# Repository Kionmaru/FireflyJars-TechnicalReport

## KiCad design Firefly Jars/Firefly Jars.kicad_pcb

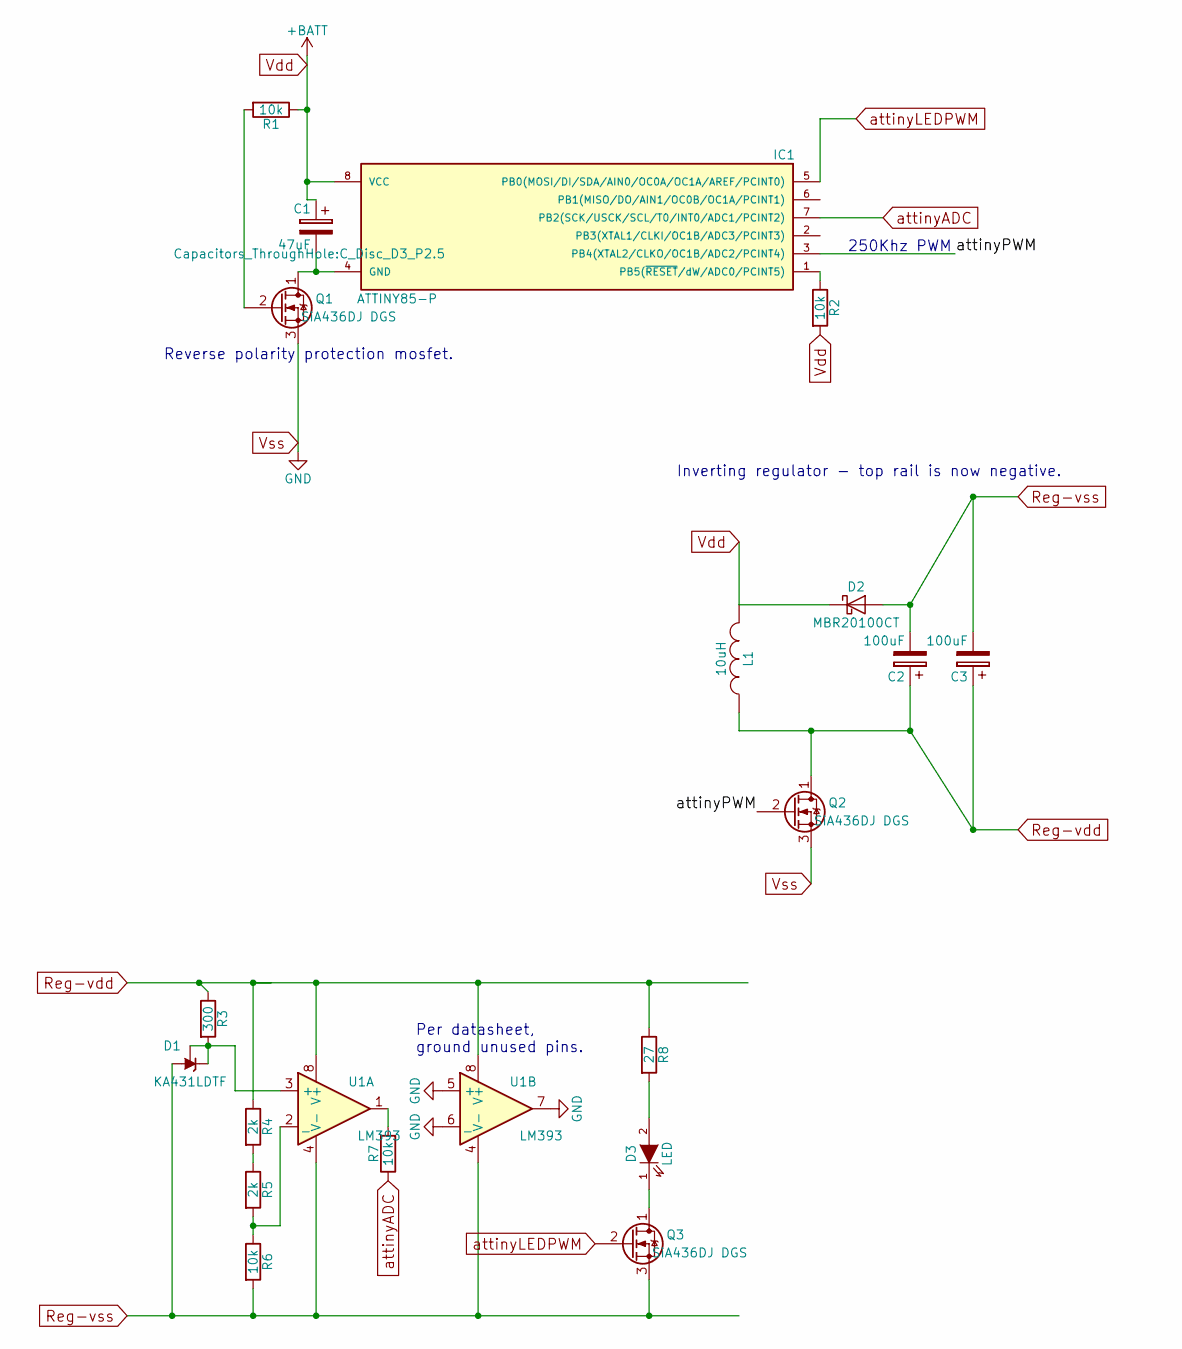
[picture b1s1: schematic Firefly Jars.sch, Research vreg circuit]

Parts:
C1: 47uF; C_Disc_D3_P2.5
C2, C3: 100uF; C_Radial_D8_L11.5_P3.5; Part No. RR71C101MDN1
D1: KA431LDTF; SOIC-8_3.9x4.9mm_Pitch1.27mm
D2: MBR20100CT; TO-220_Neutral123_Vertical
D3: LED; LED-5MM; Part No. C4SMM-RJF-CS24QBB1
IC1: ATTINY85-P; DIP-8_W7.62mm
L1: 10uH; SELF-WE-PD-XXL; Part No. ASPI-1040HI-100M-T05
Q1, Q2, Q3: SiA436DJ DGS; SC-70-6_Handsoldering; Part No. SiA436DJ
R1, R6, R7: 10k; Resistor_Horizontal_RM7mm; Part No. CF14JT10K0
R2: 10k; Resistor_Horizontal_RM7mm; Part No. Unspec'd - Not in original schematic.
R3: 300; Resistor_Horizontal_RM7mm; Part No. CF14JT300R
R4, R5: 2k; Resistor_Horizontal_RM7mm; Part No. CF14JT2K00
R8: 27; Resistor_Horizontal_RM7mm; Part No. CF14JT27R0
U1: LM393; DIP-8_W7.62mm; Part No. LM393N

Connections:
/attinyPWM: IC1.3 (PB4(XTAL2/CLKO/OC1B/ADC2/PCINT4)), Q2.2 (G)
unnamed: C1.2, IC1.4 (GND), Q1.1 (D)
unnamed: D1.1 (K), D1.8 (REF), R3.2, U1.3 (+)
unnamed: D3.1 (K), Q3.1 (D)
unnamed: D3.2 (A), R8.2
unnamed: IC1.1 (PB5(~RESET~/dW/ADC0/PCINT5)), R2.1
unnamed: Q1.2 (G), R1.2
unnamed: R4.2, R5.1
unnamed: R5.2, R6.1, U1.2 (_)
unnamed: R7.2, U1.1
Reg-vdd: C2.1, C3.1, L1.1, Q2.1 (D), R3.1, R4.1, R8.1, U1.8 (V+)
Reg-vss: C2.2, C3.2, D1.6 (A), D2.2 (A), Q3.3 (S), R6.2, U1.4 (V-)
Vdd: C1.1, D2.1 (K), IC1.8 (VCC), L1.2, R1.1, R2.2
Vss: Q1.3 (S), Q2.3 (S), U1.5 (+), U1.6 (_), U1.7
attinyADC: IC1.7 (PB2(SCK/USCK/SCL/T0/INT0/ADC1/PCINT2)), R7.1
attinyLEDPWM: IC1.5 (PB0(MOSI/DI/SDA/AIN0/OC0A/OC1A/AREF/PCI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), Q3.2 (G)

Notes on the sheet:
250Khz PWM
Inverting regulator - top rail is now negative.
Per datasheet, ground unused pins.
Reverse polarity protection mosfet.

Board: 2 copper layers, 20 parts (0 on the bottom side), 16 nets, no tracks yet.

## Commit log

2017-03-17 Initial data commit.
